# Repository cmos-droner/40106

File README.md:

# 40106 - CMOS Dronesynth
This is a basic 40106-circuit with all 6 oscillators routet. You can use it to build a simple 40106-drone-box but also more sophisticated setups are easily doable (add cv control, modulate oscillators with each other etc.)

## The circuit
The circuit is based around a single of 40106 hex-schmitt trigger.

## PCB v1
PCB v1 (in core folder) has a few bugs, which will be described soon in the build doc.

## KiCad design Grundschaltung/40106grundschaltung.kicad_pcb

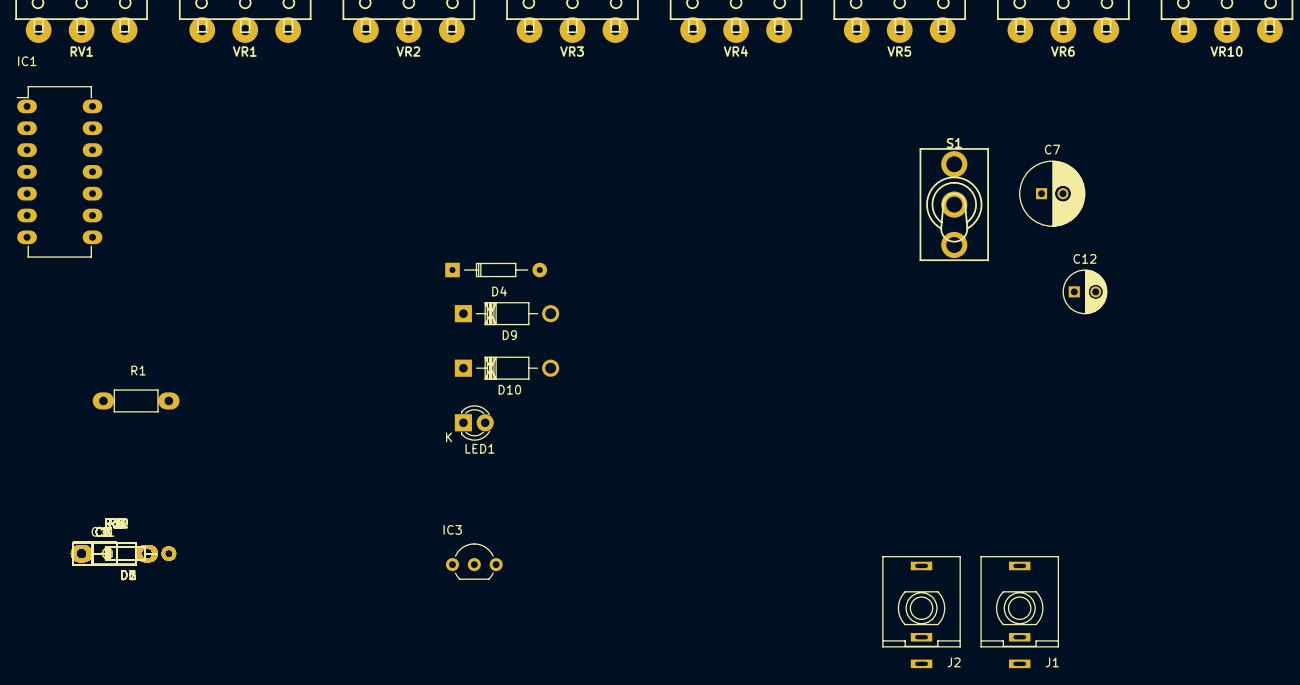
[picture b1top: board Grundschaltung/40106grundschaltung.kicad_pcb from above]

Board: 2 copper layers, 44 parts (0 on the bottom side), 16 nets, no tracks yet.

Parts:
C1, C2, C3, C4, C5, C6, C11: 0.1uF; C_Rect_L4.5_W2.5_P3
C7: 220uF; C_Radial_D7.5_L11.2_P2.5
C12: 47uF; C_Radial_D5_L11_P2.5
D1, D2, D3, D4, D5, D6: 1N4148DO35-7; Diode_DO-35_SOD27_Horizontal_RM10
D9, D10: 1N4004; Diode_DO-41_SOD81_Horizontal_RM10
IC1: 40106N; DIP-14_W7.62mm_LongPads
IC3: 78L05; TO-92_Inline_Wide
J1: DCJ0202; THONKICONN_mod
J2: CON-JACK_DCJ0202; THONKICONN_mod
LED1: LED-3MM
R1, R2, R3, R4, R5, R6: 1k; Resistor_Horizontal_RM7mm_Wide
R7, R8, R9, R10, R11, R12: 100k; Resistor_Horizontal_RM7mm_Wide
R22: 470 Ohm; Resistor_Horizontal_RM7mm_Wide
RV1: POT; R_POT_ALPHA_16MM_V
S1: SWITCH_SPDT
VR1, VR2, VR3, VR4, VR5, VR6: 1M; R_POT_ALPHA_16MM_V
VR10: 10k log; R_POT_ALPHA_16MM_V

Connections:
5V: C1.2, C2.2, C3.2, C4.2, C5.2, C6.2, C11.1, C11.2, IC1.7, J1.3, J2.1, J2.2, RV1.1, RV1.3, VR10.2
/N$1: C1.1, IC1.1, R1.2, VR1.1
/N$2: IC1.2, R12.1, VR1.2, VR1.3
/N$3: C2.1, IC1.3, R2.2, VR2.1
/N$4: IC1.4, R9.1, VR2.2, VR2.3
/N$8: C3.1, IC1.5, R3.2, VR3.1
/N$9: IC1.6, R11.1, VR3.2, VR3.3
/N$11: C4.1, IC1.8, IC1.9, R4.2, R8.1, VR4.1, VR4.2, VR4.3
/N$12: C6.1, IC1.13, R6.2, VR6.1
/N$13: C5.1, IC1.11, R5.2, VR5.1
/N$14: IC1.10, R10.1, VR5.2, VR5.3
/N$15: IC1.12, R7.1, VR6.2, VR6.3
/N$16: J2.3, R7.2, R8.2, R9.2, R10.2, R11.2, R12.2, VR10.1, VR10.3
/N$29: R22.2, S1.3
/N$34: J1.1, S1.2
unnamed: IC1.14, RV1.2

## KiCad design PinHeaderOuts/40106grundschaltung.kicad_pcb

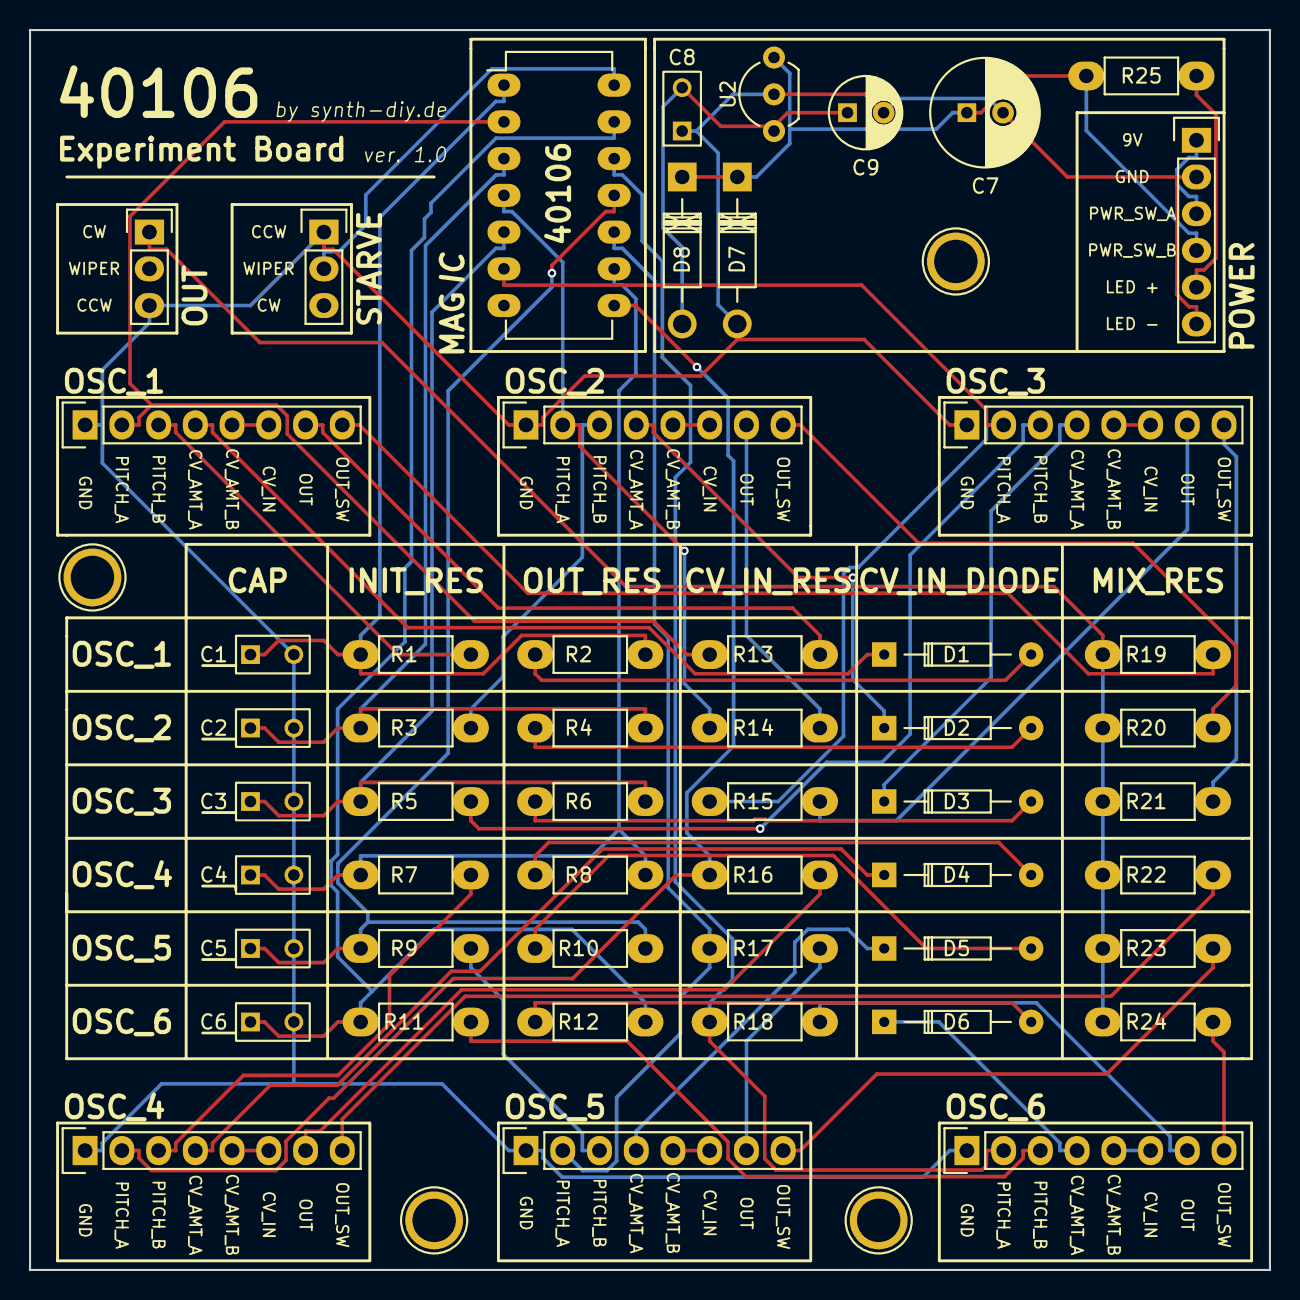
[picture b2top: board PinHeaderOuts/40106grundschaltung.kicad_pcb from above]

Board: 2 copper layers, 85.7 x 85.7 mm, 57 parts (0 on the bottom side), 55 nets.

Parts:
C1, C2, C3, C4, C5, C6, C8: 0.1uF; C_Rect_L4.5_W2.5_P3
C7: 220uF; C_Radial_D7.5_L11.2_P2.5
C9: 47uF; C_Radial_D5_L11_P2.5
D1, D2, D3, D4, D5, D6: 1N4148; Diode_DO-35_SOD27_Horizontal_RM10
D7, D8: 1N4004; Diode_DO-41_SOD81_Horizontal_RM10
H1, H2, H3, H4: 1pin
IC1: 40106; DIP-14_W7.62mm_LongPads
P1: OSC_1; Pin_Header_Straight_1x08
P2: OSC_2; Pin_Header_Straight_1x08
P3: OSC_3; Pin_Header_Straight_1x08
P4: OSC_4; Pin_Header_Straight_1x08
P5: OSC_5; Pin_Header_Straight_1x08
P6: OSC_6; Pin_Header_Straight_1x08
P7: POWER; Pin_Header_Straight_1x06
P8: STARVE; Pin_Header_Straight_1x03
P9: OUT; Pin_Header_Straight_1x03
R1, R3, R5, R7, R9, R11: 4.7k; Resistor_Horizontal_RM7mm_Wide
R2, R4, R6, R8, R10, R12, R13, R14, R15, R16, R17, R18: 1k; Resistor_Horizontal_RM7mm_Wide
R19, R20, R21, R22, R23, R24: 100k; Resistor_Horizontal_RM7mm_Wide
R25: 470 Ohm; Resistor_Horizontal_RM7mm_Wide
U2: 78L05; TO-92_Inline_Wide

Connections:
5V: C8.2, C9.1, D8.2, U2.1
GND: C1.2, C2.2, C3.2, C4.2, C5.2, C6.2, C7.2, C8.1, C9.2, D7.2, P1.1, P2.1, P3.1, P4.1, P5.1, P6.1, P7.2, P7.6, P8.1, P9.3, U2.2
unnamed: C1.1, IC1.1, R1.1, R2.2
unnamed: C2.1, IC1.3, R3.1, R4.2
unnamed: C3.1, IC1.5, R5.1, R6.2
unnamed: C4.1, IC1.9, R7.1, R8.2
unnamed: C5.1, IC1.11, R9.1, R10.2
unnamed: C6.1, IC1.13, R11.1, R12.2
unnamed: C7.1, D7.1, D8.1, P7.4, R25.2, U2.3
unnamed: D1.1, P1.4
unnamed: D1.2, R2.1
unnamed: D2.1, P2.4
unnamed: D2.2, R4.1
unnamed: D3.1, P3.4
unnamed: D3.2, R6.1
unnamed: D4.1, P4.4
unnamed: D4.2, R8.1
unnamed: D5.1, P5.4
unnamed: D5.2, R10.1
unnamed: D6.1, P6.4
unnamed: D6.2, R12.1
unnamed: IC1.2, P1.2, R13.1
unnamed: IC1.4, P2.2, R14.1
unnamed: IC1.6, P3.2, R15.1
unnamed: IC1.8, P4.2, R16.1
unnamed: IC1.10, P5.2, R17.1
unnamed: IC1.12, P6.2, R18.1
unnamed: IC1.14, P8.2
unnamed: P1.3, R1.2
unnamed: P1.5, P1.6
unnamed: P1.7, R13.2
unnamed: P1.8, R19.2
unnamed: P2.3, R3.2
unnamed: P2.5, P2.6
unnamed: P2.7, R14.2
unnamed: P2.8, R20.2
unnamed: P3.3, R5.2
unnamed: P3.5, P3.6
unnamed: P3.7, R15.2
unnamed: P3.8, R21.2
unnamed: P4.3, R7.2
unnamed: P4.5, P4.6
unnamed: P4.7, R16.2
unnamed: P4.8, R22.2
unnamed: P5.3, R9.2
unnamed: P5.5, P5.6
unnamed: P5.7, R17.2
unnamed: P5.8, R23.2
unnamed: P6.3, R11.2
unnamed: P6.5, P6.6
unnamed: P6.7, R18.2
unnamed: P6.8, R24.2
unnamed: P7.1, P7.3
unnamed: P7.5, R25.1
unnamed: P9.1, R19.1, R20.1, R21.1, R22.1, R23.1, R24.1

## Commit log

2017-01-28 remove duplicates and rename folder
2017-01-28 add readme and build-guide dummy
2017-01-28 type
